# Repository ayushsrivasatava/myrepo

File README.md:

In this i have made a transformer less power suppply which can convert a 220v ac power supply to 5v dc supply at receiver end . the layout and schematic is drawn in ki cad . and this is my first time with ki cad and git hub .

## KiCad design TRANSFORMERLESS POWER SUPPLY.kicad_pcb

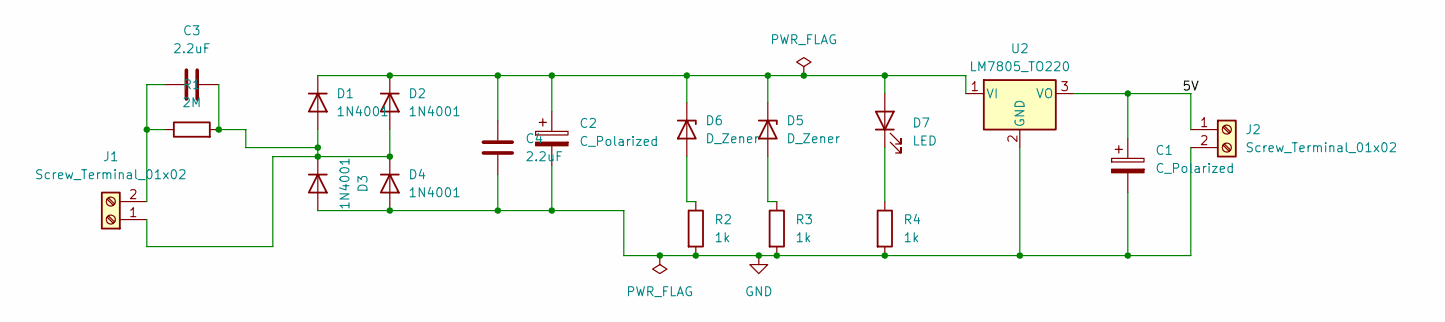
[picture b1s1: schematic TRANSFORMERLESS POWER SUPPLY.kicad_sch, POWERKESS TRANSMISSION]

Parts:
C1: C_Polarized; C_Disc_D7.5mm_W5.0mm_P7.50mm
C2: C_Polarized; C_Radial_D6.3mm_H5.0mm_P2.50mm
C3: 2.2uF; CP_Radial_D7.5mm_P2.50mm
C4: 2.2uF; C_Rect_L4.0mm_W2.5mm_P2.50mm
D1, D2, D3, D4: 1N4001; D_DO-41_SOD81_P10.16mm_Horizontal
D5, D6: D_Zener; D_5W_P10.16mm_Horizontal
D7: LED; LED_D5.0mm
J1, J2: Screw_Terminal_01x02; TerminalBlock_Altech_AK300-2_P5.00mm
R1: 2M; R_Axial_DIN0411_L9.9mm_D3.6mm_P15.24mm_Horizontal
R2, R3, R4: 1k; R_Axial_DIN0411_L9.9mm_D3.6mm_P15.24mm_Horizontal
U2: LM7805_TO220; TO-220-3_Vertical

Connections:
/5V: C1.1, J2.1, U2.3 (VO)
GND: C1.2, C2.2, C4.1, D3.2 (A), D4.2 (A), J2.2, R2.2, R3.2, R4.2, U2.2 (GND)
unnamed: C3.2, D1.2 (A), D2.2 (A), D3.1 (K), D4.1 (K), J1.1, R1.2
unnamed: C2.1, C4.2, D1.1 (K), D2.1 (K), D5.1 (K), D6.1 (K), D7.2 (A), U2.1 (VI)
unnamed: D5.2 (A), R3.1
unnamed: D6.2 (A), R2.1
unnamed: D7.1 (K), R4.1
unnamed: C3.1, J1.2, R1.1

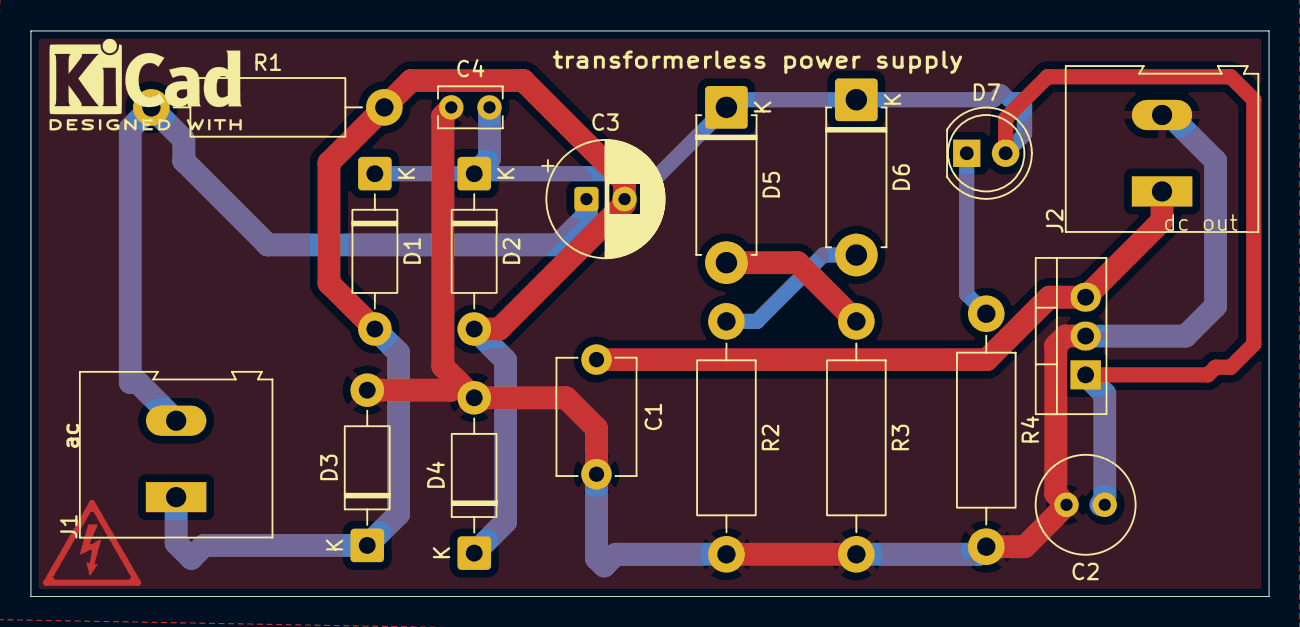
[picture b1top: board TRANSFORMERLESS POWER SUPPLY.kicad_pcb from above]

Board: 2 copper layers, 81.0 x 37.0 mm, 18 parts (0 on the bottom side), 8 nets.

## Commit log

2025-06-29 Initail commit
